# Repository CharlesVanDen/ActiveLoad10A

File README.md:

# ActiveLoad10A
A simple DIY Active Load up to 10A and 100W. Analog, only Constant Current
Project description at https://charlesouweland.wordpress.com/2020/01/30/diy-active-load/

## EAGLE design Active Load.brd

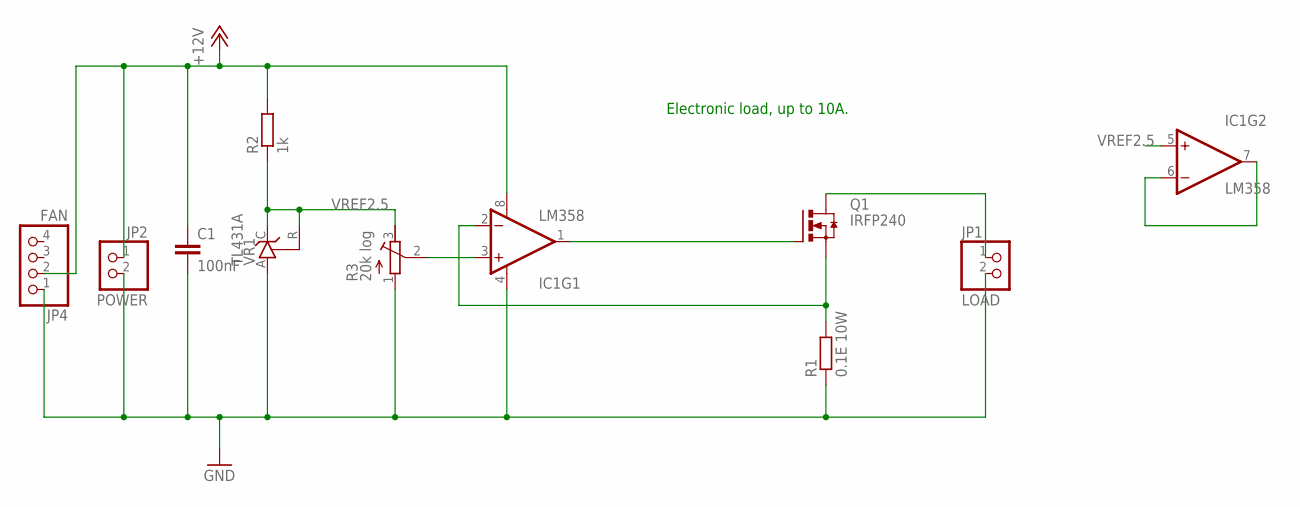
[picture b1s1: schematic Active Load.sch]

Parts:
C1: 100nF; C025-040X050
IC1: LM358; DIP08
JP1: LOAD; 1X02
JP2: POWER; 1X02
JP4: FAN; 1X04
Q1: IRFP240; TO247BV
R1: 0.1E 10W; 0922/22
R2: 1k; 0411/12
R3: 20k log; RTRIM74W
VR1: TL431A; TO92-CLP

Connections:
+12V: C1.1, IC1.8 (V+), JP2.1, JP4.2, R2.2
GND: C1.2, IC1.4 (V-), JP1.2, JP2.2, JP4.1, R1.1, R3.1 (A), VR1.A
unnamed: IC1.6 (-IN), IC1.7 (OUT)
unnamed: IC1.3 (+IN), R3.2 (S)
unnamed: IC1.2 (-IN), Q1.S, R1.2
unnamed: IC1.1 (OUT), Q1.G
unnamed: JP1.1, Q1.D
VREF2.5: IC1.5 (+IN), R2.1, R3.3 (E), VR1.C, VR1.R

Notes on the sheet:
Electronic load, up to 10A.

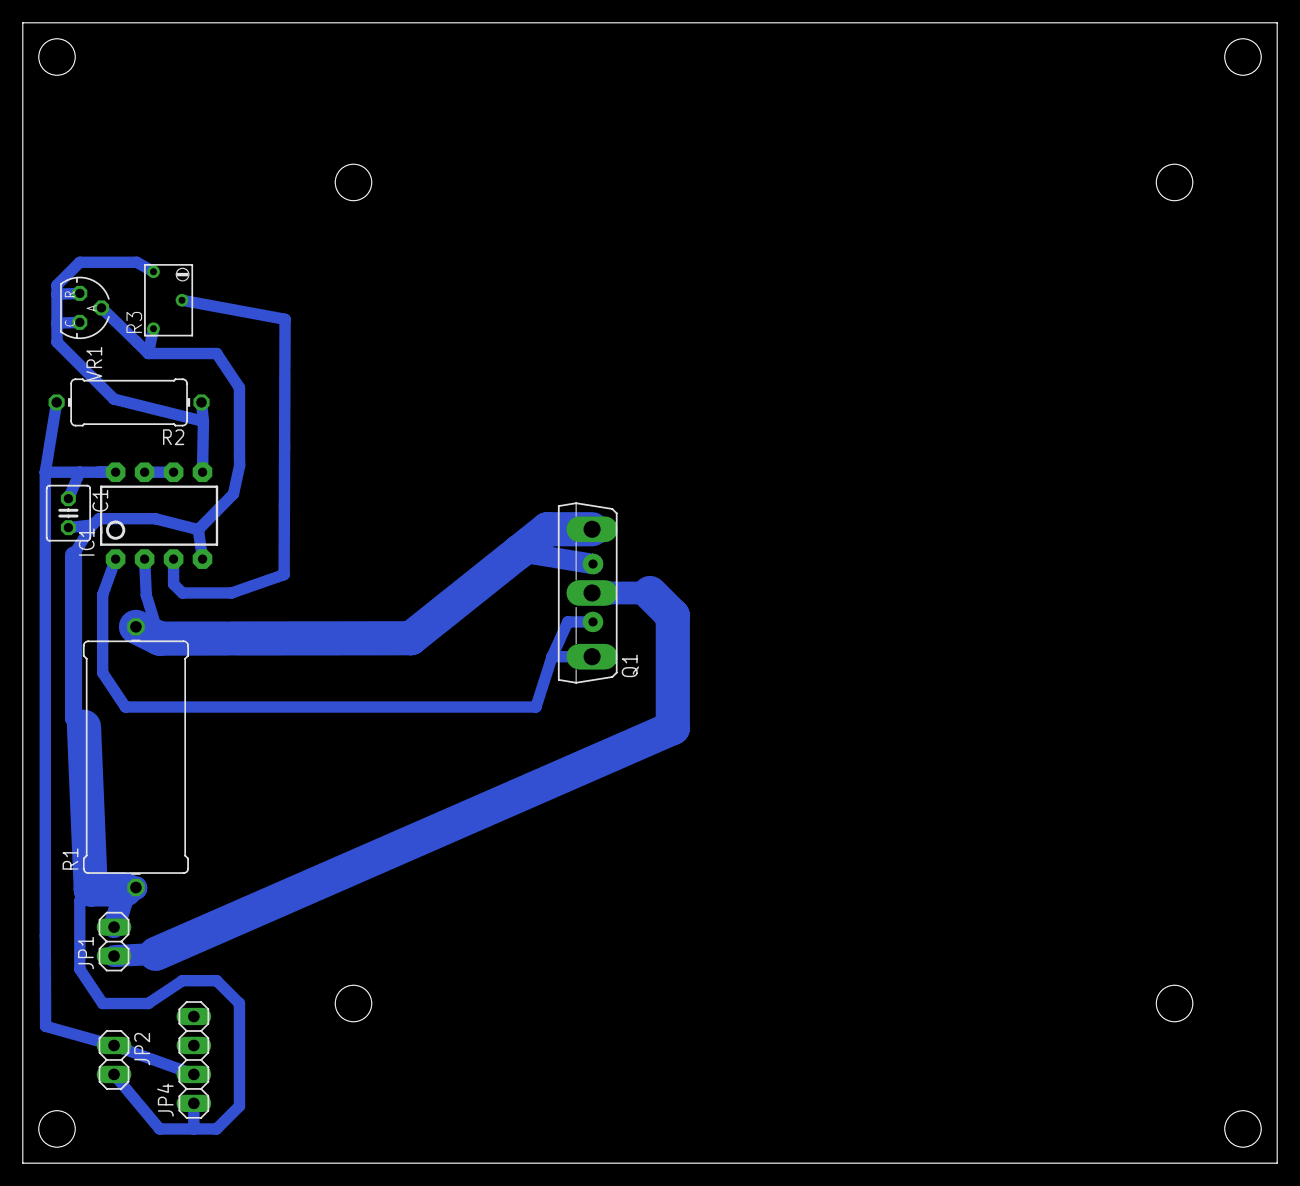
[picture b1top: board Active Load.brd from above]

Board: 2 copper layers, 110.0 x 100.0 mm, 10 parts (0 on the bottom side), 8 nets.

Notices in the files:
parts and their libraries:
SparkFun-AnalogIC: Licensing:Creative Commons ShareAlike 4.0 International - https://creativecommons.org/licenses/by-sa/4.0
